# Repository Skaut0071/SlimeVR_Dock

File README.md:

# SlimeVR\_Dock

Continuation of the tracker project: https://github.com/Skaut0071/SlimeVR_Tracker

This repository contains a smart (overengineered) charging dock station for my previously designed SlimeVR FBT trackers.

The dock is built around an ESP32-C3, which controls the charging system and provides protection logic for connected trackers if a fault condition occurs.

## Features

* 8 USB-C charging ports (J2-J9), arranged as 4 dual-port channels
* Powered from a single USB-C PD input (20V / 3A, negotiated by a CH224K), stepped down to 5V (up to 8.5A) for the ports
* Per-port voltage/current monitoring with an INA226 (8x) over I2C
* Overcurrent protection and per-channel enable/fault handling with an AP22652 load switch (4x)
* Temperature/humidity monitoring (BME280 module on the I2C header)
* 4-pin PWM fan header with tachometer input, driven by the ESP32-C3
* Audible error alerts through an on-board buzzer
* Wireless connectivity over Wi-Fi

## Hardware overview

| Block | Main parts | Notes |
| --- | --- | --- |
| MCU | ESP32-C3-WROOM-02 (U1) | Controls charging, reads monitors, handles faults |
| Power input | USB-C receptacle (J1\_MainPW1), CH224K (U2), NDT452AP (Q1) | Requests 20V from a PD source |
| 5V step-down | TPS548A20 (U4), 2.2uH inductor (L1) | 20V to 5V, 8.5A |
| 3V3 regulator | XC6220B331MR (U3) | Powers the ESP32-C3 and logic |
| Charging channels (x4) | 2x USB-C, 2x INA226, AP22652 load switch, BC857 | Each channel serves two ports; see schematic sheet below |
| I/O expansion | 2x 74HC165 (U17, U18), 74HC595 (U19) | Shift registers for reading channel status and sending control signals |
| Headers | Control, Monitor, Prog (3-pin), Temp (4-pin), Fan (4-pin) | Dev/debug access, sensor and fan connectors |
| Buzzer | BZ1 | Error alerts |

The board is a 2-layer, 1.6mm PCB, roughly 100 x 78 mm (JLCPCB gerbers included).

## Schematic structure

The design is hierarchical (KiCad):

| Sheet | File | Description |
| --- | --- | --- |
| Root - SlimeVR Dock (rev 3.1) | `Board/SlimeVR_Dock.kicad_sch` | MCU, PD input, 3V3 regulator, shift registers, connectors, buzzer |
| 20V to 5V 8.5A Stepdown (rev 2.1) | `Board/StepDown.kicad_sch` | TPS548A20 buck converter |
| Dual USB-C charger monitoring (rev 1.8) | `Board/DUSBSS.kicad_sch` | Instantiated 4x; load switch, protection and detection for a pair of ports |
| Overcurrent protection (rev 1.2) | `Board/USB-C.kicad_sch` | USB-C connector with INA226 current measurement, instantiated 2x per channel |

The PCB is currently at rev 5 (`Board/SlimeVR_Dock.kicad_pcb`).

## Firmware flashing note

To flash new firmware versions, you must use the internal programming pins (`Prog` header).
Or in future, firmware flashing over web interface of the device.

USB-C cannot be used for flashing in this design, because the same USB connection is used to power the board.

## Repository layout

* `Board/` - KiCad project (schematics, PCB, custom footprints in `Library.pretty`)
* `Gerb/` - Gerber/fabrication files for JLCPCB
* `PDF/` - PDF schematic, BOM (CSV) and interactive BOM
* `3D/` - 3D model exports

## Interactive BOM

* [Interactive BOM](https://skaut0071.github.io/SlimeVR_Dock/PDF/ibom.html)

## PDF Schematic

* [PDF Schematic](https://skaut0071.github.io/SlimeVR_Dock/PDF/SlimeVR_Dock.pdf)

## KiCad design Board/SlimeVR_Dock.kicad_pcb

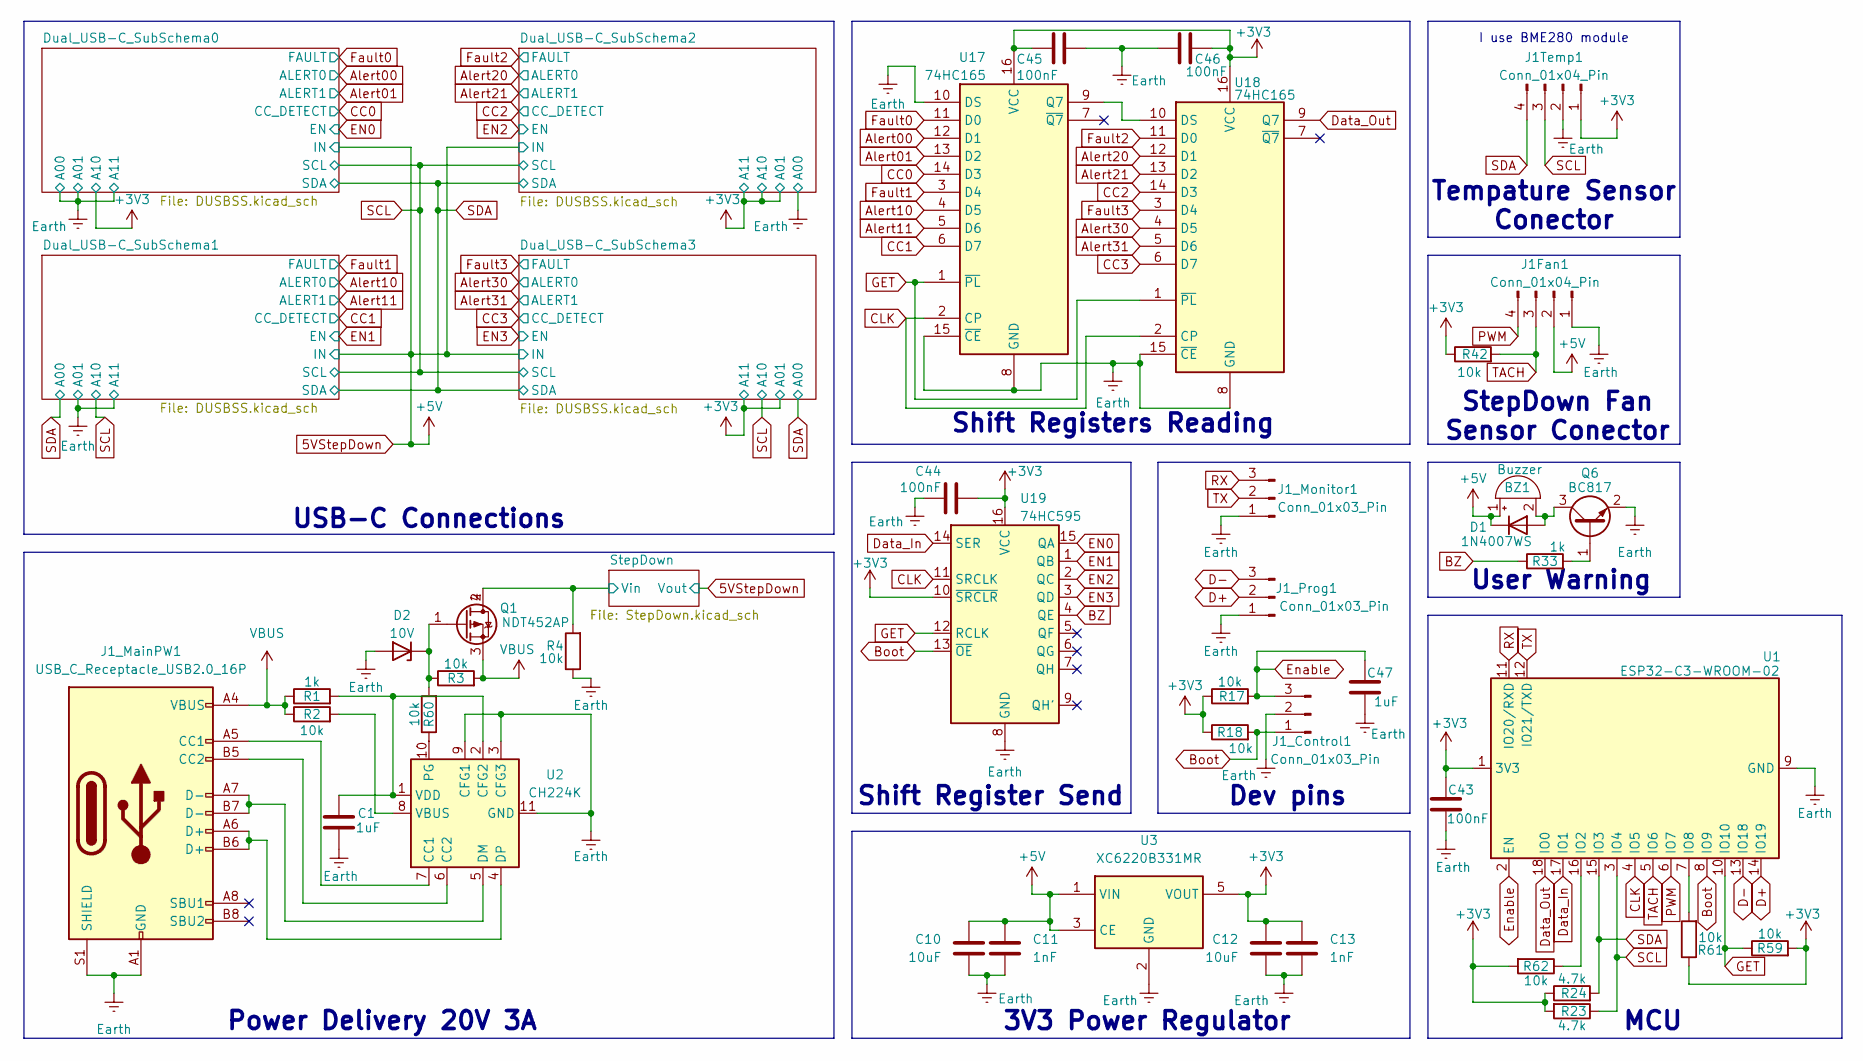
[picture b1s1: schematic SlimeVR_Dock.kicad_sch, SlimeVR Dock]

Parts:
BZ1: Buzzer; Buzzer_12x9.5RM7.6; LCSC alr - Any passive buzzer
C1, C47: 1uF; C_0603_1608Metric; LCSC C15849
C10, C12: 10uF; C_0603_1608Metric; LCSC alr C19702
C11, C13: 1nF; C_0603_1608Metric; LCSC alr C100040
C43, C44, C45, C46: 100nF; C_0603_1608Metric; LCSC alr C6119867
D1: 1N4007WS; D_SOD-323; LCSC alr C7473299
D2: 10V; D_SOD-123; LCSC alr C47117498
J1Fan1: Conn_01x04_Pin; FanPinHeader_1x04_P2.54mm_Vertical; LCSC alr C240840
J1Temp1: Conn_01x04_Pin; PinHeader_1x04_P2.54mm_Vertical; LCSC x - Only holes
J1_Control1, J1_Monitor1, J1_Prog1: Conn_01x03_Pin; PinHeader_1x03_P2.54mm_Vertical; LCSC x - Only holes
J1_MainPW1: USB_C_Receptacle_USB2.0_16P; USB_C_Receptacle_GCT_USB4105-xx-A_16P_TopMnt_Horizontal; LCSC alr C5178539
Q1: NDT452AP; SOT-223; LCSC alr C274614
Q6: BC817; SOT-23; LCSC alr C39828
R1: 1k; R_2010_5025Metric; LCSC C2974087
R2, R3, R4, R17, R18, R42, R59, R60, R61, R62: 10k; R_0603_1608Metric; LCSC alr C98220
R23, R24: 4.7k; R_0603_1608Metric; LCSC alr C99782
R33: 1k; R_0603_1608Metric; LCSC alr C22548
U1: ESP32-C3-WROOM-02; LCSC C2934560
U2: CH224K; SSOP-10-1EP_3.9x4.9mm_P1mm_EP2.1x3.3mm; LCSC alr C970725
U3: XC6220B331MR; SOT-23-5; LCSC alr C86534
U17, U18: 74HC165; SOIC-16_3.9x9.9mm_P1.27mm; LCSC alr C5613
U19: 74HC595; SOIC-16_3.9x9.9mm_P1.27mm; LCSC alr C5947

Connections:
5VStepDown: BZ1.1 (+), C10.1, C11.1, D1.1 (K), J1Fan1.2, U3.1 (VIN), U3.3 (CE); also elsewhere on the board
+3V3: C12.1, C13.1, C43.1, C44.2, C45.2, C46.1, J1Temp1.1, R17.1, R18.1, R23.2, R24.1, R42.1, R59.2, R61.1, R62.2, U1.1 (3V3), U3.5 (VOUT), U17.16 (VCC), U18.16 (VCC), U19.10 (~SRCLR), U19.16 (VCC); also elsewhere on the board
/StepDown/Vin: Q1.2 (D), Q1.4 (D), R4.2; also elsewhere on the board
Alert00: U17.12 (D1); also elsewhere on the board
Alert01: U17.13 (D2); also elsewhere on the board
Alert10: U17.4 (D5); also elsewhere on the board
Alert11: U17.5 (D6); also elsewhere on the board
Alert20: U18.12 (D1); also elsewhere on the board
Alert21: U18.13 (D2); also elsewhere on the board
Alert30: U18.4 (D5); also elsewhere on the board
Alert31: U18.5 (D6); also elsewhere on the board
BZ: R33.1, U19.4 (QE)
Boot: J1_Control1.1, R18.2, U1.8 (IO9), U19.13 (~OE)
CC0: U17.14 (D3); also elsewhere on the board
CC1: U17.6 (D7); also elsewhere on the board
CC2: U18.14 (D3); also elsewhere on the board
CC3: U18.6 (D7); also elsewhere on the board
CLK: U1.4 (IO5), U17.2 (CP), U18.2 (CP), U19.11 (SRCLK)
D+: J1_Prog1.2, U1.14 (IO19)
D-: J1_Prog1.3, U1.13 (IO18)
Data_In: U1.17 (IO1), U19.14 (SER)
Data_Out: U1.18 (IO0), U18.9 (Q7)
EN0: U19.15 (QA); also elsewhere on the board
EN1: U19.1 (QB); also elsewhere on the board
EN2: U19.2 (QC); also elsewhere on the board
EN3: U19.3 (QD); also elsewhere on the board
Earth: C1.1, C10.2, C11.2, C12.2, C13.2, C43.2, C44.1, C45.1, C46.2, C47.2, D2.2 (A), J1Fan1.1, J1Temp1.2, J1_Control1.2, J1_MainPW1.A1 (GND), J1_MainPW1.A12 (GND), J1_MainPW1.B1 (GND), J1_MainPW1.B12 (GND), J1_MainPW1.S1 (SHIELD), J1_Monitor1.1, J1_Prog1.1, Q6.2 (E), R4.1, U1.9 (GND), U1.19 (GND), U2.3 (CFG3), U2.9 (CFG1), U2.11 (GND), U3.2 (GND), U17.8 (GND), U17.10 (DS), U17.15 (~CE), U18.8 (GND), U18.15 (~CE), U19.8 (GND); also elsewhere on the board
Enable: C47.1, J1_Control1.3, R17.2, U1.2 (EN)
Fault0: U17.11 (D0); also elsewhere on the board
Fault1: U17.3 (D4); also elsewhere on the board
Fault2: U18.11 (D0); also elsewhere on the board
Fault3: U18.3 (D4); also elsewhere on the board
GET: R59.1, U1.10 (IO10), U17.1 (~PL), U18.1 (~PL), U19.12 (RCLK)
unnamed: BZ1.2 (-), D1.2 (A), Q6.3 (C)
unnamed: D2.1 (K), Q1.1 (G), R3.1, R60.2
unnamed: J1_MainPW1.A5 (CC1), U2.7 (CC1)
unnamed: J1_MainPW1.B5 (CC2), U2.6 (CC2)
unnamed: Q6.1 (B), R33.2
unnamed: R62.1, U1.16 (IO2)
unnamed: R61.2, U1.7 (IO8)
unnamed: C1.2, R1.2, U2.1 (VDD), U2.2 (CFG2)
unnamed: J1_MainPW1.A7 (D-), J1_MainPW1.B7 (D-), U2.5 (DM)
unnamed: J1_MainPW1.A6 (D+), J1_MainPW1.B6 (D+), U2.4 (DP)
unnamed: R60.1, U2.10 (PG)
unnamed: R2.2, U2.8 (VBUS)
unnamed: U17.9 (Q7), U18.10 (DS)
PWM: J1Fan1.4, U1.6 (IO7)
RX: J1_Monitor1.3, U1.11 (IO20/RXD)
SCL: J1Temp1.3, R23.1, U1.3 (IO4); also elsewhere on the board
SDA: J1Temp1.4, R24.2, U1.15 (IO3); also elsewhere on the board
TACH: J1Fan1.3, R42.2, U1.5 (IO6)
TX: J1_Monitor1.2, U1.12 (IO21/TXD)
VBUS: J1_MainPW1.A4 (VBUS), J1_MainPW1.A9 (VBUS), J1_MainPW1.B4 (VBUS), J1_MainPW1.B9 (VBUS), Q1.3 (S), R1.1, R2.1, R3.2

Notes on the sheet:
User Warning
MCU
Tempature Sensor Conector
Shift Registers Reading
3V3 Power Regulator
Power Delivery 20V 3A
I use BME280 module
Dev pins
USB-C Connections
StepDown Fan Sensor Conector
Shift Register Send

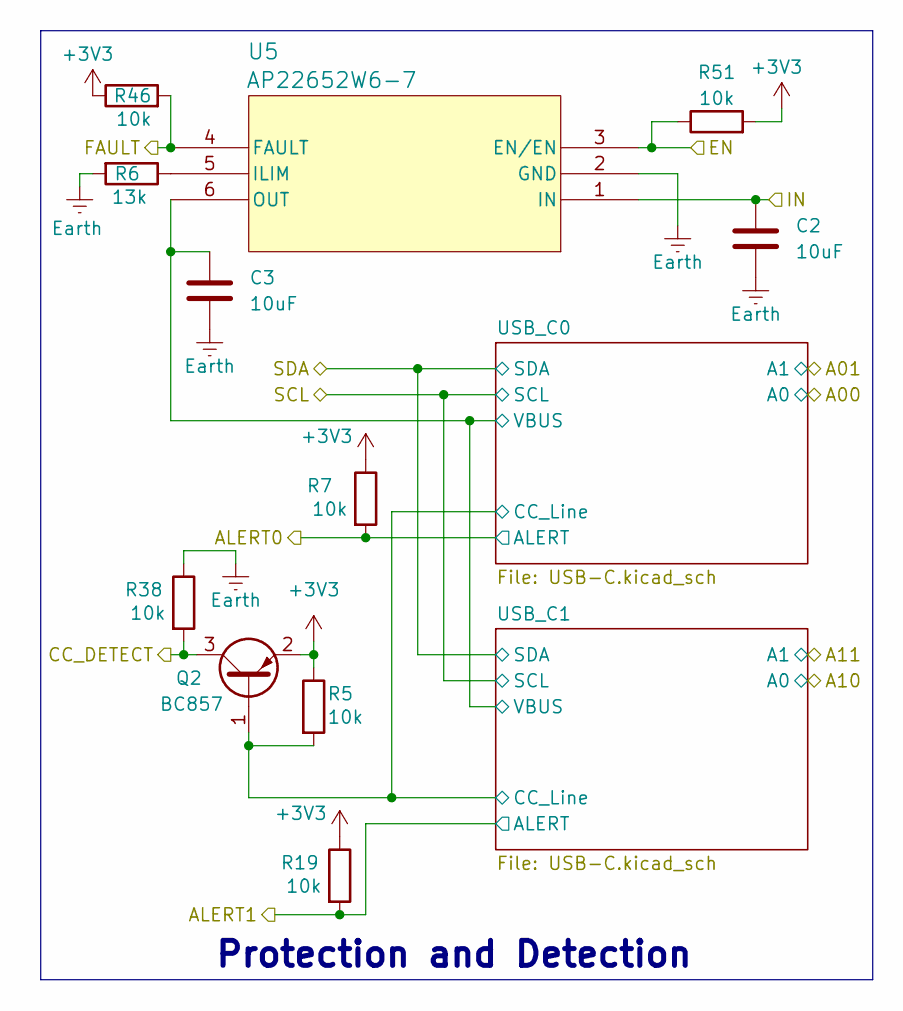
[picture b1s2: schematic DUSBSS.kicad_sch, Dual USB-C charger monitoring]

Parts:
C2, C3: 10uF; C_0603_1608Metric; LCSC alr C19702
Q2: BC857; SOT-23; LCSC alr C111644
R5, R7, R19, R38, R46, R51: 10k; R_0603_1608Metric; LCSC alr C98220
R6: 13k; R_0603_1608Metric; LCSC C54920854
U5: AP22652W6-7; SOIC_52W6-7_DIO; LCSC alr C2158038

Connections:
5VStepDown: C2.1, U5.1 (IN); also elsewhere on the board
+3V3: Q2.2 (E), R5.1, R7.1, R19.1, R46.1, R51.2; also elsewhere on the board
/Dual_USB-C_SubSchema0/USB_C0/CC_Line: Q2.1 (B), R5.2; also elsewhere on the board
/Dual_USB-C_SubSchema0/USB_C0/VBUS: C3.1, U5.6 (OUT); also elsewhere on the board
Alert00: R7.2; also elsewhere on the board
Alert01: R19.2; also elsewhere on the board
CC0: Q2.3 (C), R38.2; also elsewhere on the board
EN0: R51.1, U5.3 (EN/EN); also elsewhere on the board
Earth: C2.2, C3.2, R6.2, R38.1, U5.2 (GND); also elsewhere on the board
Fault0: R46.2, U5.4 (FAULT); also elsewhere on the board
unnamed: R6.1, U5.5 (ILIM)

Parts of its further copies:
C4, C5, C6, C7, C8, C9: 10uF; C_0603_1608Metric; LCSC alr C19702
Q3, Q4, Q5: BC857; SOT-23; LCSC alr C111644
R8, R10, R11, R13, R14, R16, R20, R21, R22, R43, R44, R45, R47, R48, R49, R52, R53, R58: 10k; R_0603_1608Metric; LCSC alr C98220
R9, R12, R15: 13k; R_0603_1608Metric; LCSC C54920854
U8, U11, U14: AP22652W6-7; SOIC_52W6-7_DIO; LCSC alr C2158038

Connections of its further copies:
5VStepDown: C4.1, C6.1, C8.1, U8.1 (IN), U11.1 (IN), U14.1 (IN); also elsewhere on the board
+3V3: Q3.2 (E), Q4.2 (E), Q5.2 (E), R8.1, R10.1, R11.1, R13.1, R14.1, R16.1, R20.1, R21.1, R22.1, R47.1, R48.1, R49.1, R52.2, R53.2, R58.2; also elsewhere on the board
/Dual_USB-C_SubSchema1/USB_C0/CC_Line: Q3.1 (B), R8.2; also elsewhere on the board
/Dual_USB-C_SubSchema1/USB_C0/VBUS: C5.1, U8.6 (OUT); also elsewhere on the board
/Dual_USB-C_SubSchema2/USB_C0/CC_Line: Q4.1 (B), R11.2; also elsewhere on the board
/Dual_USB-C_SubSchema2/USB_C0/VBUS: C7.1, U11.6 (OUT); also elsewhere on the board
/Dual_USB-C_SubSchema3/USB_C0/CC_Line: Q5.1 (B), R14.2; also elsewhere on the board
/Dual_USB-C_SubSchema3/USB_C0/VBUS: C9.1, U14.6 (OUT); also elsewhere on the board
Alert10: R10.2; also elsewhere on the board
Alert11: R20.2; also elsewhere on the board
Alert20: R13.2; also elsewhere on the board
Alert21: R21.2; also elsewhere on the board
Alert30: R16.2; also elsewhere on the board
Alert31: R22.2; also elsewhere on the board
CC1: Q3.3 (C), R43.2; also elsewhere on the board
CC2: Q4.3 (C), R44.2; also elsewhere on the board
CC3: Q5.3 (C), R45.2; also elsewhere on the board
EN1: R52.1, U8.3 (EN/EN); also elsewhere on the board
EN2: R53.1, U11.3 (EN/EN); also elsewhere on the board
EN3: R58.1, U14.3 (EN/EN); also elsewhere on the board
Earth: C4.2, C5.2, C6.2, C7.2, C8.2, C9.2, R9.2, R12.2, R15.2, R43.1, R44.1, R45.1, U8.2 (GND), U11.2 (GND), U14.2 (GND); also elsewhere on the board
Fault1: R47.2, U8.4 (FAULT); also elsewhere on the board
Fault2: R48.2, U11.4 (FAULT); also elsewhere on the board
Fault3: R49.2, U14.4 (FAULT); also elsewhere on the board
unnamed: R9.1, U8.5 (ILIM)
unnamed: R12.1, U11.5 (ILIM)
unnamed: R15.1, U14.5 (ILIM)

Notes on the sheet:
Protection and Detection

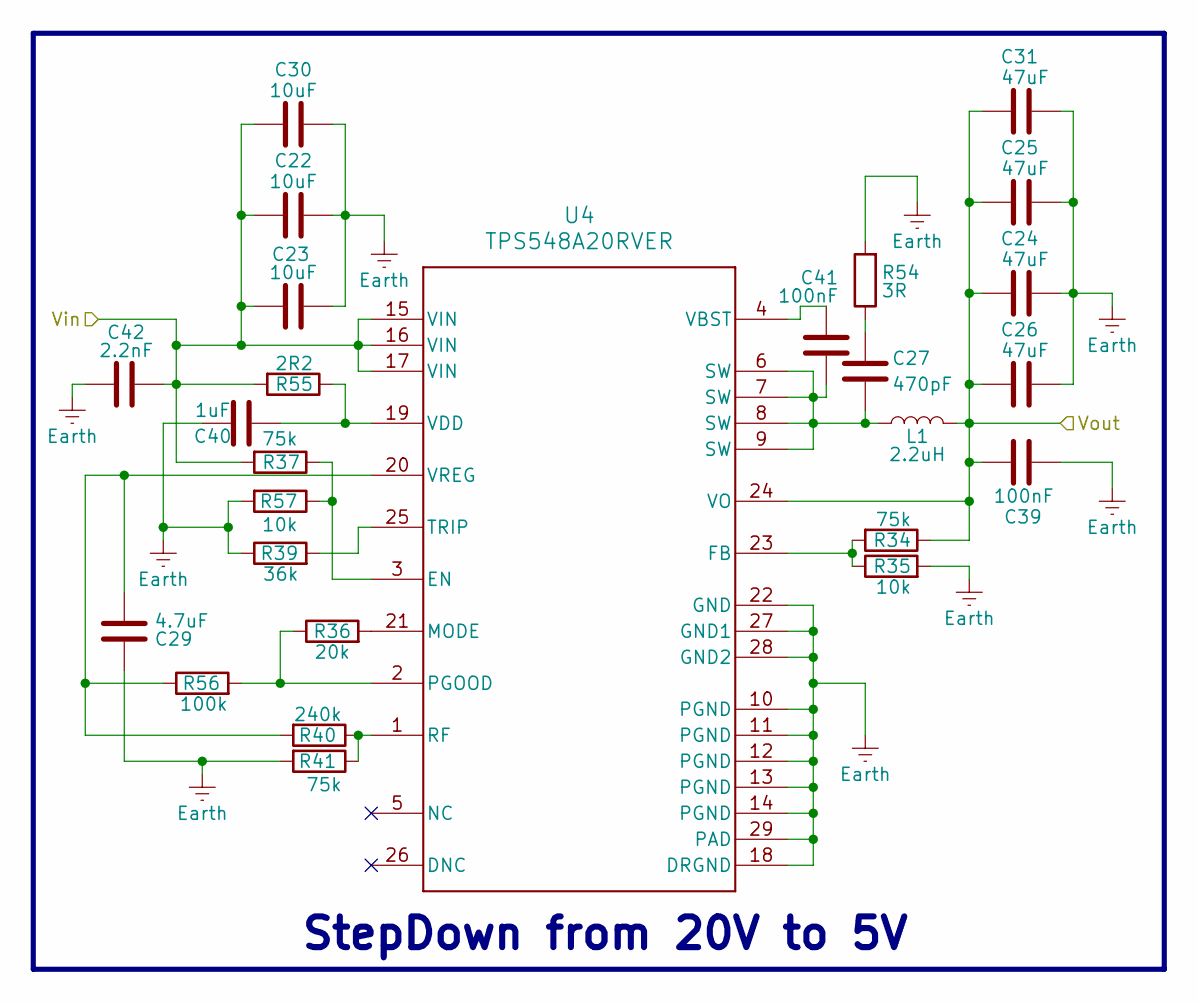
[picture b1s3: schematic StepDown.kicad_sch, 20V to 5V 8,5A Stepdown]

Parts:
C22, C23, C30: 10uF; C_1210_3225Metric; LCSC alr C47117451
C24, C25, C26, C31: 47uF; C_0805_2012Metric; LCSC alr C16780
C27: 470pF; C_0805_2012Metric; LCSC C1743
C29: 4.7uF; C_0805_2012Metric; LCSC alr C98192
C39, C41: 100nF; C_0805_2012Metric; LCSC alr C49678
C40: 1uF; C_0603_1608Metric; LCSC C15849
C42: 2.2nF; C_0402_1005Metric; LCSC C1531
L1: 2.2uH; L_Coilank_APS0730; LCSC C49261221
R34, R37, R41: 75k; R_0603_1608Metric; LCSC alr C2907067
R35, R57: 10k; R_0603_1608Metric; LCSC alr C98220
R36: 20k; R_0603_1608Metric; LCSC C2907011
R39: 36k; R_0603_1608Metric; LCSC C54531400
R40: 240k; R_0603_1608Metric; LCSC alr C4197
R54: 3R; R_0805_2012Metric; LCSC C17660
R55: 2R2; R_0603_1608Metric; LCSC C2907006
R56: 100k; R_0603_1608Metric; LCSC alr C14675
U4: TPS548A20RVER; RVE0028A; LCSC alr C468255

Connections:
5VStepDown: C24.1, C25.1, C26.1, C31.1, C39.2, L1.2, R34.1, U4.24 (VO); also elsewhere on the board
/StepDown/Vin: C22.1, C23.1, C30.1, C42.1, R37.2, R55.2, U4.15 (VIN), U4.16 (VIN), U4.17 (VIN); also elsewhere on the board
Earth: C22.2, C23.2, C24.2, C25.2, C26.2, C29.1, C30.2, C31.2, C39.1, C40.1, C42.2, R35.2, R39.1, R41.2, R54.2, R57.2, U4.10 (PGND), U4.11 (PGND), U4.12 (PGND), U4.13 (PGND), U4.14 (PGND), U4.18 (DRGND), U4.22 (GND), U4.27 (GND1), U4.28 (GND2), U4.29 (PAD); also elsewhere on the board
unnamed: C27.1, R54.1
unnamed: C27.2, C41.1, L1.1, U4.6 (SW), U4.7 (SW), U4.8 (SW), U4.9 (SW)
unnamed: R37.1, R57.1, U4.3 (EN)
unnamed: R34.2, R35.1, U4.23 (FB)
unnamed: R36.2, U4.21 (MODE)
unnamed: R36.1, R56.2, U4.2 (PGOOD)
unnamed: R40.1, R41.1, U4.1 (RF)
unnamed: R39.2, U4.25 (TRIP)
unnamed: C41.2, U4.4 (VBST)
unnamed: C40.2, R55.1, U4.19 (VDD)
unnamed: C29.2, R40.2, R56.1, U4.20 (VREG)

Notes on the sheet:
StepDown from 20V to 5V

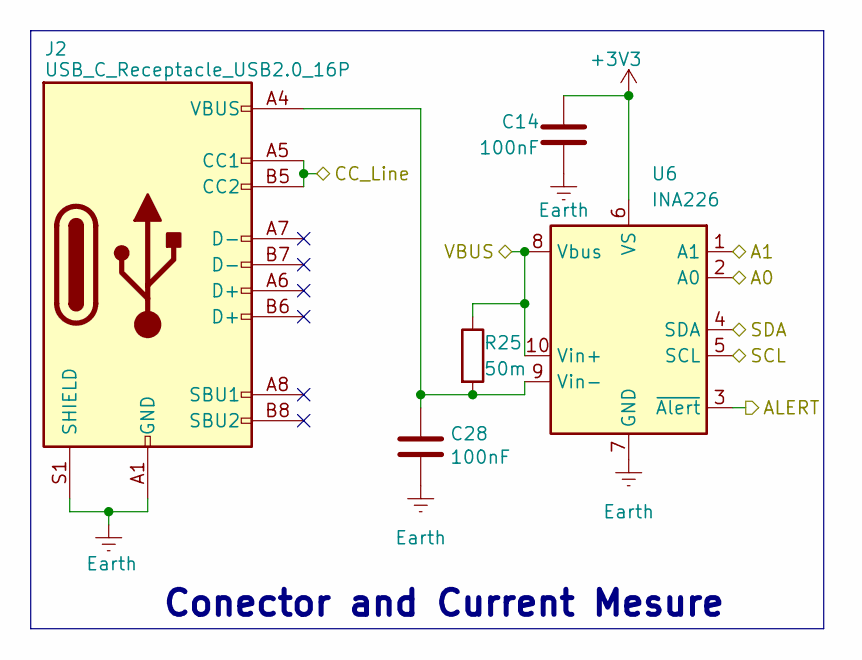
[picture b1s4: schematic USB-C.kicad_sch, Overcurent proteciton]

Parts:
C14, C28: 100nF; C_0603_1608Metric; LCSC alr C6119867
J2: USB_C_Receptacle_USB2.0_16P; YTC-TC16S-128; LCSC alr C2927282
R25: 50m; R_0805_2012Metric; LCSC C42389461
U6: INA226; VSSOP-10_3x3mm_P0.5mm; LCSC alr C49851

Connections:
+3V3: C14.1, U6.6 (VS); also elsewhere on the board
/Dual_USB-C_SubSchema0/USB_C0/CC_Line: J2.A5 (CC1), J2.B5 (CC2); also elsewhere on the board
/Dual_USB-C_SubSchema0/USB_C0/VBUS: R25.1, U6.8 (Vbus), U6.10 (Vin+); also elsewhere on the board
Alert00: U6.3 (~Alert); also elsewhere on the board
Earth: C14.2, C28.1, J2.A1 (GND), J2.A12 (GND), J2.B1 (GND), J2.B12 (GND), J2.S1 (SHIELD), U6.1 (A1), U6.2 (A0), U6.7 (GND); also elsewhere on the board
unnamed: C28.2, J2.A4 (VBUS), J2.A9 (VBUS), J2.B4 (VBUS), J2.B9 (VBUS), R25.2, U6.9 (Vin-)
SCL: U6.5 (SCL); also elsewhere on the board
SDA: U6.4 (SDA); also elsewhere on the board

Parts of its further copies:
C15, C16, C17, C18, C19, C20, C21, C32, C33, C34, C35, C36, C37, C38: 100nF; C_0603_1608Metric; LCSC alr C6119867
J3, J4, J5, J6, J7, J8, J9: USB_C_Receptacle_USB2.0_16P; YTC-TC16S-128; LCSC alr C2927282
R26, R27, R28, R29, R30, R31, R32: 50m; R_0805_2012Metric; LCSC C42389461
U7, U9, U10, U12, U13, U15, U16: INA226; VSSOP-10_3x3mm_P0.5mm; LCSC alr C49851

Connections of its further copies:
+3V3: C15.1, C16.1, C17.1, C18.1, C19.1, C20.1, C21.1, U7.2 (A0), U7.6 (VS), U9.6 (VS), U10.6 (VS), U12.1 (A1), U12.6 (VS), U13.1 (A1), U13.2 (A0), U13.6 (VS), U15.1 (A1), U15.6 (VS), U16.1 (A1), U16.6 (VS); also elsewhere on the board
/Dual_USB-C_SubSchema0/USB_C0/CC_Line: J3.A5 (CC1), J3.B5 (CC2); also elsewhere on the board
/Dual_USB-C_SubSchema0/USB_C0/VBUS: R26.1, U7.8 (Vbus), U7.10 (Vin+); also elsewhere on the board
/Dual_USB-C_SubSchema1/USB_C0/CC_Line: J4.A5 (CC1), J4.B5 (CC2), J5.A5 (CC1), J5.B5 (CC2); also elsewhere on the board
/Dual_USB-C_SubSchema1/USB_C0/VBUS: R27.1, R28.1, U9.8 (Vbus), U9.10 (Vin+), U10.8 (Vbus), U10.10 (Vin+); also elsewhere on the board
/Dual_USB-C_SubSchema2/USB_C0/CC_Line: J6.A5 (CC1), J6.B5 (CC2), J7.A5 (CC1), J7.B5 (CC2); also elsewhere on the board
/Dual_USB-C_SubSchema2/USB_C0/VBUS: R29.1, R30.1, U12.8 (Vbus), U12.10 (Vin+), U13.8 (Vbus), U13.10 (Vin+); also elsewhere on the board
/Dual_USB-C_SubSchema3/USB_C0/CC_Line: J8.A5 (CC1), J8.B5 (CC2), J9.A5 (CC1), J9.B5 (CC2); also elsewhere on the board
/Dual_USB-C_SubSchema3/USB_C0/VBUS: R31.1, R32.1, U15.8 (Vbus), U15.10 (Vin+), U16.8 (Vbus), U16.10 (Vin+); also elsewhere on the board
Alert01: U7.3 (~Alert); also elsewhere on the board
Alert10: U9.3 (~Alert); also elsewhere on the board
Alert11: U10.3 (~Alert); also elsewhere on the board
Alert20: U12.3 (~Alert); also elsewhere on the board
Alert21: U13.3 (~Alert); also elsewhere on the board
Alert30: U15.3 (~Alert); also elsewhere on the board
Alert31: U16.3 (~Alert); also elsewhere on the board
Earth: C15.2, C16.2, C17.2, C18.2, C19.2, C20.2, C21.2, C32.1, C33.1, C34.1, C35.1, C36.1, C37.1, C38.1, J3.A1 (GND), J3.A12 (GND), J3.B1 (GND), J3.B12 (GND), J3.S1 (SHIELD), J4.A1 (GND), J4.A12 (GND), J4.B1 (GND), J4.B12 (GND), J4.S1 (SHIELD), J5.A1 (GND), J5.A12 (GND), J5.B1 (GND), J5.B12 (GND), J5.S1 (SHIELD), J6.A1 (GND), J6.A12 (GND), J6.B1 (GND), J6.B12 (GND), J6.S1 (SHIELD), J7.A1 (GND), J7.A12 (GND), J7.B1 (GND), J7.B12 (GND), J7.S1 (SHIELD), J8.A1 (GND), J8.A12 (GND), J8.B1 (GND), J8.B12 (GND), J8.S1 (SHIELD), J9.A1 (GND), J9.A12 (GND), J9.B1 (GND), J9.B12 (GND), J9.S1 (SHIELD), U7.1 (A1), U7.7 (GND), U9.1 (A1), U9.7 (GND), U10.1 (A1), U10.7 (GND), U12.2 (A0), U12.7 (GND), U13.7 (GND), U15.7 (GND), U16.7 (GND); also elsewhere on the board
unnamed: C32.2, J3.A4 (VBUS), J3.A9 (VBUS), J3.B4 (VBUS), J3.B9 (VBUS), R26.2, U7.9 (Vin-)
unnamed: C34.2, J4.A4 (VBUS), J4.A9 (VBUS), J4.B4 (VBUS), J4.B9 (VBUS), R28.2, U9.9 (Vin-)
unnamed: C33.2, J5.A4 (VBUS), J5.A9 (VBUS), J5.B4 (VBUS), J5.B9 (VBUS), R27.2, U10.9 (Vin-)
unnamed: C36.2, J6.A4 (VBUS), J6.A9 (VBUS), J6.B4 (VBUS), J6.B9 (VBUS), R30.2, U12.9 (Vin-)
unnamed: C35.2, J7.A4 (VBUS), J7.A9 (VBUS), J7.B4 (VBUS), J7.B9 (VBUS), R29.2, U13.9 (Vin-)
unnamed: C38.2, J8.A4 (VBUS), J8.A9 (VBUS), J8.B4 (VBUS), J8.B9 (VBUS), R32.2, U15.9 (Vin-)
unnamed: C37.2, J9.A4 (VBUS), J9.A9 (VBUS), J9.B4 (VBUS), J9.B9 (VBUS), R31.2, U16.9 (Vin-)
SCL: U7.5 (SCL), U9.5 (SCL), U10.2 (A0), U10.5 (SCL), U12.5 (SCL), U13.5 (SCL), U15.5 (SCL), U16.2 (A0), U16.5 (SCL); also elsewhere on the board
SDA: U7.4 (SDA), U9.2 (A0), U9.4 (SDA), U10.4 (SDA), U12.4 (SDA), U13.4 (SDA), U15.2 (A0), U15.4 (SDA), U16.4 (SDA); also elsewhere on the board

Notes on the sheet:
Conector and Current Mesure

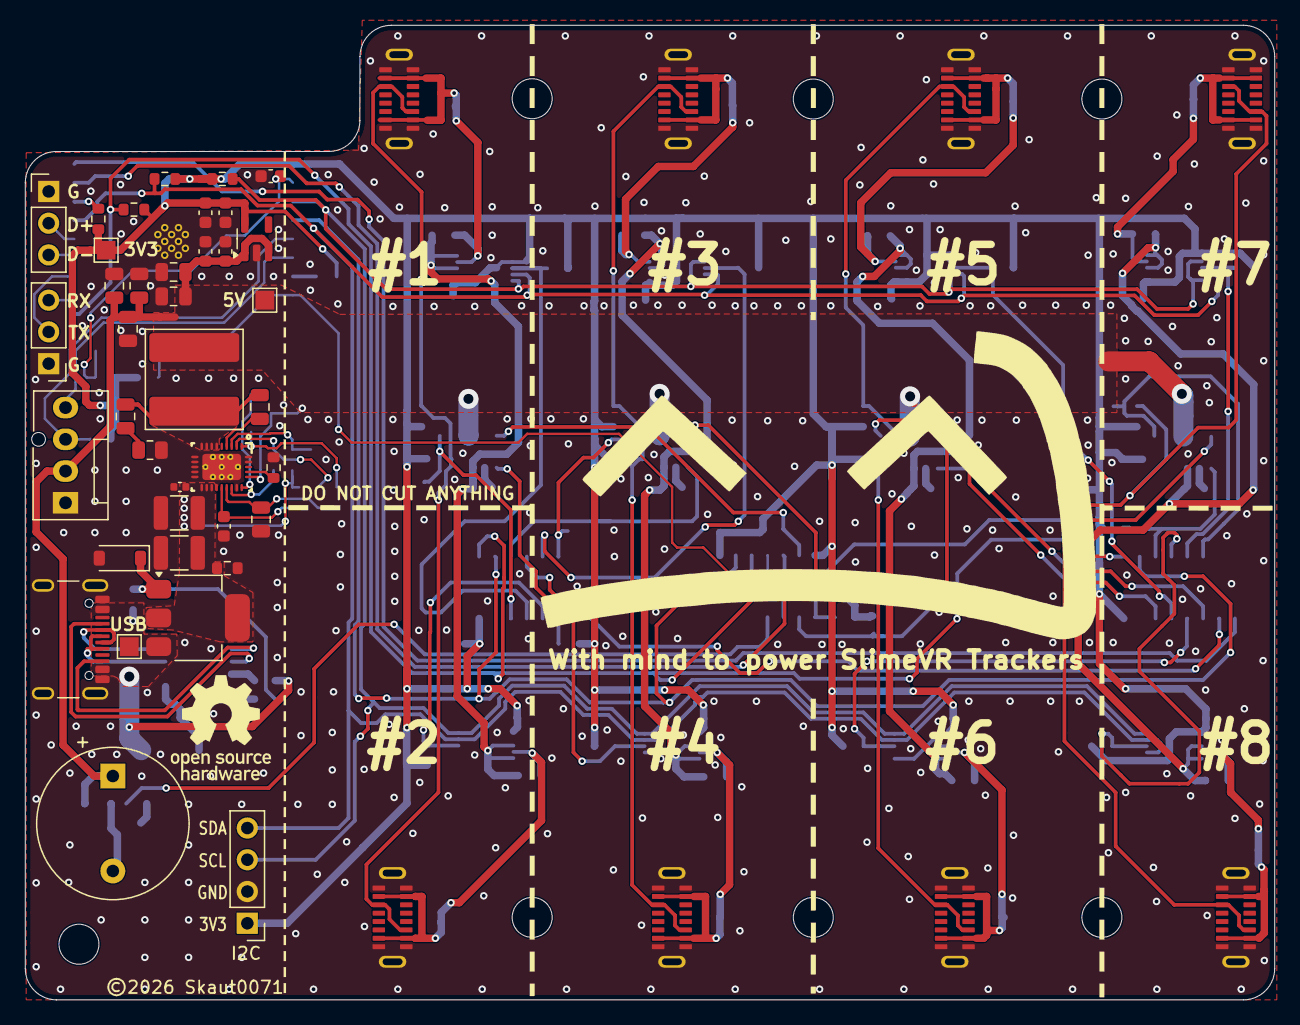
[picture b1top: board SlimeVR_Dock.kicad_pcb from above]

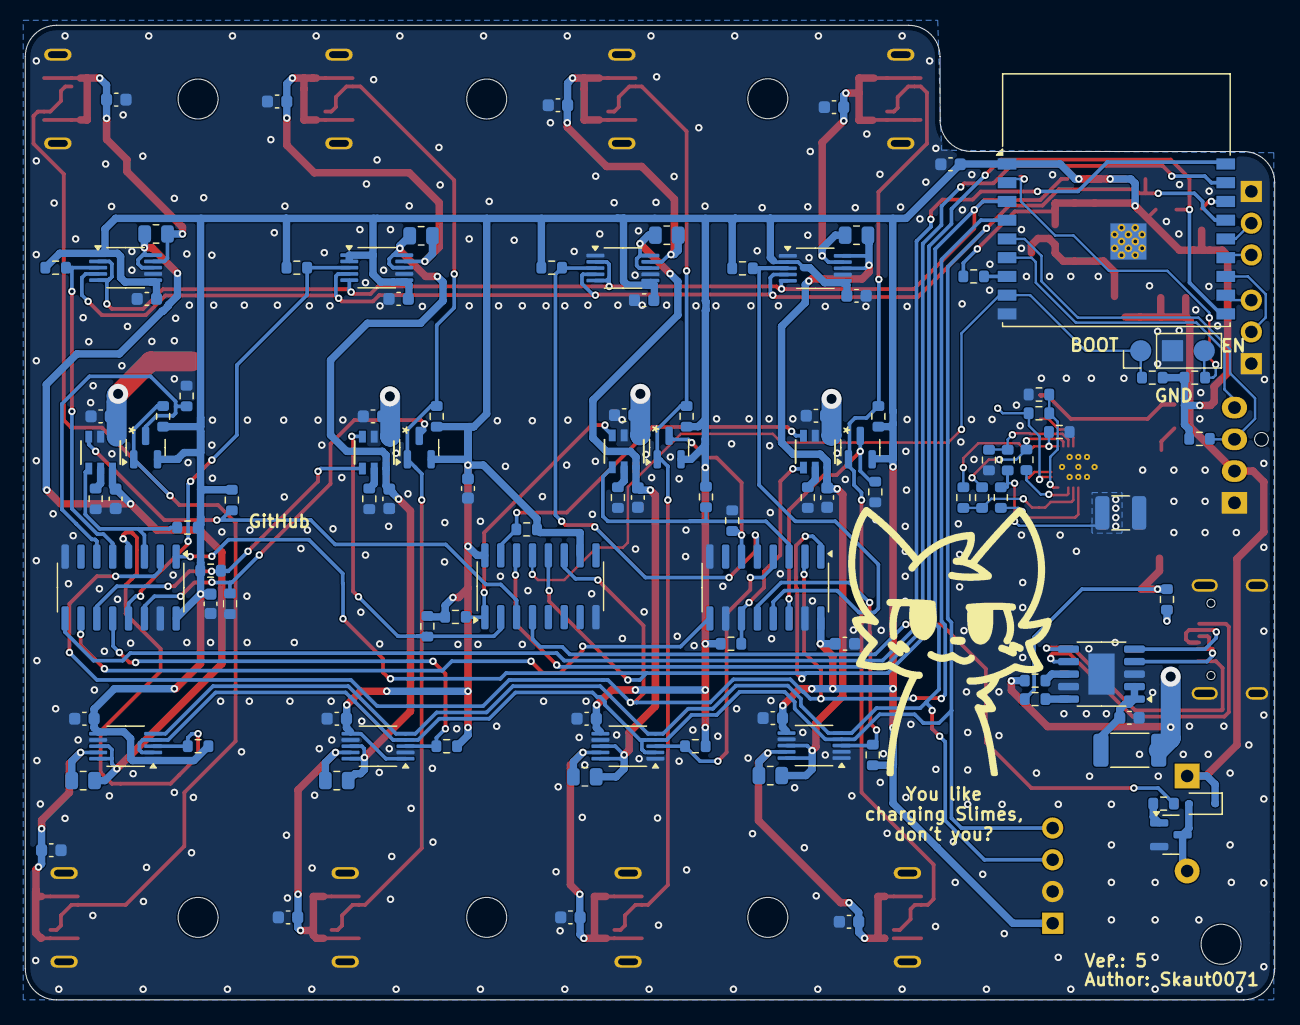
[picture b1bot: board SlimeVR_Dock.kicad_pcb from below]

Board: 2 copper layers, 100.0 x 78.0 mm, 154 parts (108 on the bottom side), 84 nets.

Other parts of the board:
3V3, 5V: TestPoint_Pad_1.5x1.5mm
USB: TestPoint_Pad_1.5x1.5mm

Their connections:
5VStepDown: 5V.1; also elsewhere on the board
+3V3: 3V3.1; also elsewhere on the board

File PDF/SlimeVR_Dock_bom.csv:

"Reference","Qty","Value","Footprint","#","LCSC"
"C27","1","470pF","Capacitor_SMD:C_0805_2012Metric","1","C1743"
"C11,C13","2","1nF","Capacitor_SMD:C_0603_1608Metric","2","alr C100040"
"C42","1","2.2nF","Capacitor_SMD:C_0402_1005Metric","3","C1531"
"C14,C15,C16,C17,C18,C19,C20,C21,C28,C32,C33,C34,C35,C36,C37,C38,C43,C44,C45,C46","20","100nF","Capacitor_SMD:C_0603_1608Metric","4","alr C6119867"
"C39,C41","2","100nF","Capacitor_SMD:C_0805_2012Metric","5","alr C49678"
"C1,C40,C47","3","1uF","Capacitor_SMD:C_0603_1608Metric","6","C15849"
"L1","1","2.2uH","Library:L_Coilank_APS0730","7","C49261221"
"C29","1","4.7uF","Capacitor_SMD:C_0805_2012Metric","8","alr C98192"
"C2,C3,C4,C5,C6,C7,C8,C9,C10,C12","10","10uF","Capacitor_SMD:C_0603_1608Metric","9","alr C19702"
"C22,C23,C30","3","10uF","Capacitor_SMD:C_1210_3225Metric","10","alr C47117451"
"C24,C25,C26,C31","4","47uF","Capacitor_SMD:C_0805_2012Metric","11","alr C16780"
"R25,R26,R27,R28,R29,R30,R31,R32","8","50m","Resistor_SMD:R_0805_2012Metric","12","C42389461"
"R55","1","2R2","Resistor_SMD:R_0603_1608Metric","13","C2907006"
"R54","1","3R","Resistor_SMD:R_0805_2012Metric","14","C17660"
"D2","1","10V","Diode_SMD:D_SOD-123","15","alr C47117498"
"R1","1","1k","Resistor_SMD:R_2010_5025Metric","16","C2974087"
"R33","1","1k","Resistor_SMD:R_0603_1608Metric","17","alr C22548"
"R23,R24","2","4.7k","Resistor_SMD:R_0603_1608Metric","18","alr C99782"
"R2,R3,R4,R5,R7,R8,R10,R11,R13,R14,R16,R17,R18,R19,R20,R21,R22,R35,R38,R42,R43,R44,R45,R46,R47,R48,R49,R51,R52,R53,R57,R58,R59,R60,R61,R62","36","10k","Resistor_SMD:R_0603_1608Metric","19","alr C98220"
"R6,R9,R12,R15","4","13k","Resistor_SMD:R_0603_1608Metric","20","C54920854"
"R36","1","20k","Resistor_SMD:R_0603_1608Metric","21","C2907011"
"R39","1","36k","Resistor_SMD:R_0603_1608Metric","22","C54531400"
"R34,R37,R41","3","75k","Resistor_SMD:R_0603_1608Metric","23","alr C2907067"
"R56","1","100k","Resistor_SMD:R_0603_1608Metric","24","alr C14675"
"R40","1","240k","Resistor_SMD:R_0603_1608Metric","25","alr C4197"
"D1","1","1N4007WS","Diode_SMD:D_SOD-323","26","alr C7473299"
"U17,U18","2","74HC165","Package_SO:SOIC-16_3.9x9.9mm_P1.27mm","27","alr C5613"
"U19","1","74HC595","Package_SO:SOIC-16_3.9x9.9mm_P1.27mm","28","alr C5947"
"U5,U8,U11,U14","4","AP22652W6-7","Library:SOIC_52W6-7_DIO","29","alr C2158038"
"Q6","1","BC817","Package_TO_SOT_SMD:SOT-23","30","alr C39828"
"Q2,Q3,Q4,Q5","4","BC857","Package_TO_SOT_SMD:SOT-23","31","alr C111644"
"BZ1","1","Buzzer","Buzzer_Beeper:Buzzer_12x9.5RM7.6","32","alr - Any passive buzzer"
"U2","1","CH224K","Package_SO:SSOP-10-1EP_3.9x4.9mm_P1mm_EP2.1x3.3mm","33","alr C970725"
"J1_Control1,J1_Monitor1,J1_Prog1","3","Conn_01x03_Pin","Connector_PinHeader_2.54mm:PinHeader_1x03_P2.54mm_Vertical","34","x - Only holes"
"J1Fan1","1","Conn_01x04_Pin","Connector:FanPinHeader_1x04_P2.54mm_Vertical","35","alr C240840"
"J1Temp1","1","Conn_01x04_Pin","Connector_PinHeader_2.54mm:PinHeader_1x04_P2.54mm_Vertical","36","x - Only holes"
"U1","1","ESP32-C3-WROOM-02","RF_Module:ESP32-C3-WROOM-02","37","C2934560"
"U6,U7,U9,U10,U12,U13,U15,U16","8","INA226","Package_SO:VSSOP-10_3x3mm_P0.5mm","38","alr C49851"
"Q1","1","NDT452AP","Package_TO_SOT_SMD:SOT-223","39","alr C274614"
"U4","1","TPS548A20RVER","Library:RVE0028A","40","alr C468255"
"J1_MainPW1","1","USB_C_Receptacle_USB2.0_16P","Connector_USB:USB_C_Receptacle_GCT_USB4105-xx-A_16P_TopMnt_Horizontal","41","alr C5178539"
"J2,J3,J4,J5,J6,J7,J8,J9","8","USB_C_Receptacle_USB2.0_16P","Library:YTC-TC16S-128","42","alr C2927282"
"U3","1","XC6220B331MR","Package_TO_SOT_SMD:SOT-23-5","43","alr C86534"

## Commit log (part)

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2026-01-09 Init and pd
    created repositary nad created basic schema with conected power delivery
2026-01-10 Moved files
    from /board/slimevr_dock/ to /board/
2026-01-10 made subschema for usb-c
    subschea for USB-Cs for more comact schema
2026-01-10 New Layout and power
    Made power for 3v3
    all usb added
2026-01-11 Saving pins
    -4 pins to connect to gpio thanks for ability to use two or more alert pins on one gpio
2026-01-15 Conecting usb to esp
    added in/out and out/in reistry
2026-01-16 Finished Schematic
2026-01-25 Updavení USB-C
2026-04-05 layout
    -bude asi potreba jiny footrpint usb-c
2026-04-07 Custom StepDown
2026-04-07 minority upravy
2026-04-08 pcb layout
2026-04-09 upraveni veliskoti
2026-04-09 prvni segment usb-c
2026-04-09 pokus o posunutí cívky
2026-04-09 almost finished layout V1
2026-04-10 leyout finished
    - needs silkscreen modification
    - usb-c footprint
2026-04-10 Complete
    -fixed tach pullup missing
    - may have some unrecognised issues
2026-04-11 Small changes
2026-04-11 fixed chema, finished silkscreen
    -Alert10 was duplicated
2026-04-11 Updated fields for LCSC
2026-04-11 Created greb
2026-04-11 misspeling
2026-04-11 Ready for Manifacture
2026-04-11 updated bom
2026-04-11 Update ReadMe, added references
2026-04-11 better references
2026-04-11 fixed reference in readme and english translation
2026-04-17 new pdf schema
2026-04-21 Update links in README to use absolute URLs
2026-05-10 Version 2
    - Fixed StepDown stabilization 5V output - probebly idk :D
2026-05-10 Fix Layout
2026-05-11 Fixed CC_detect transistor
2026-05-11 fixed grounding and updated to kicad 10
2026-05-11 DRC fix
2026-05-15 Update ibom
2026-05-16 Total Power Suply layout overhall
2026-05-16 New Power
2026-05-16 Fixed zener diode orientation
2026-05-16 Version 3
    Hopefully it works idk ?:D
2026-05-16 Ground plane edits
2026-05-17 RC on coil outut and VDD resistor added
2026-05-17 edited silkscreen
2026-05-17 fixed pad
2026-05-17 Changed baed on sugestions
2026-05-17 added caps to outputs
2026-05-17 updated by sugestions
2026-05-17 fixed via in pad
2026-05-17 caps reorangement
2026-05-17 fix silkscreen
2026-05-20 Updated documentation

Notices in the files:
Board/SlimeVR_Dock.kicad_pcb:
©2026 Skaut0071
